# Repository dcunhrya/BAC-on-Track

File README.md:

# BAC-on-Track
Wearable Breathalyzer connected to an app to detect BAC levels for college students

This repo contains:
Circuit schematics from KiCAD,
PCB Layout from KiCAD,
OnShape CAD design

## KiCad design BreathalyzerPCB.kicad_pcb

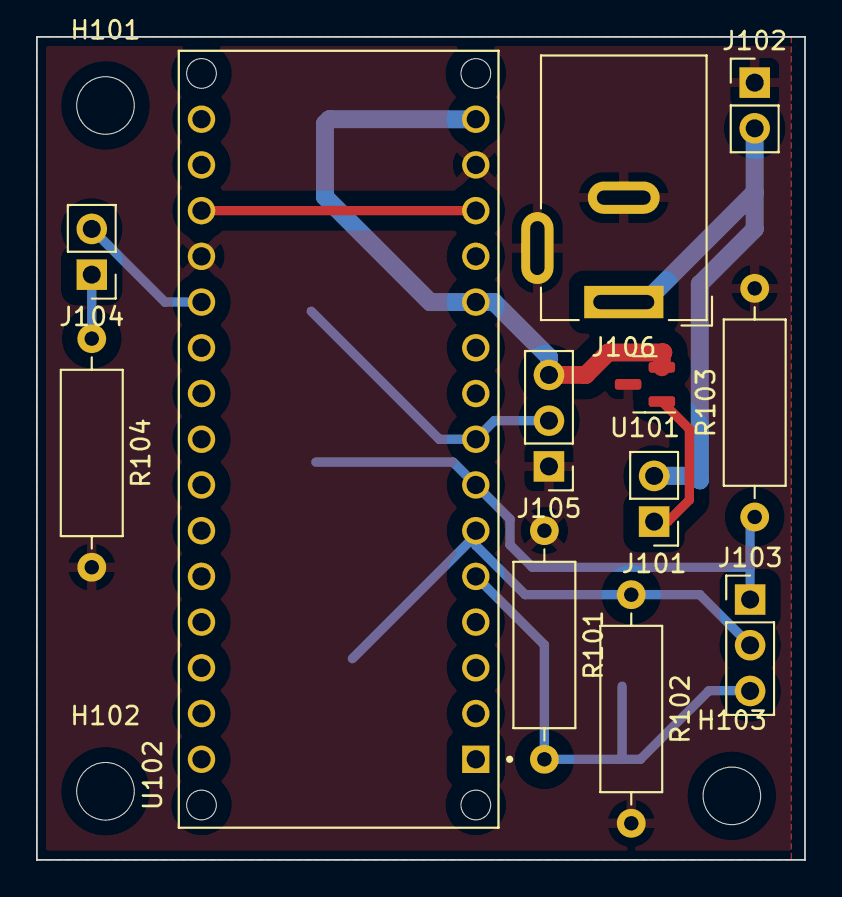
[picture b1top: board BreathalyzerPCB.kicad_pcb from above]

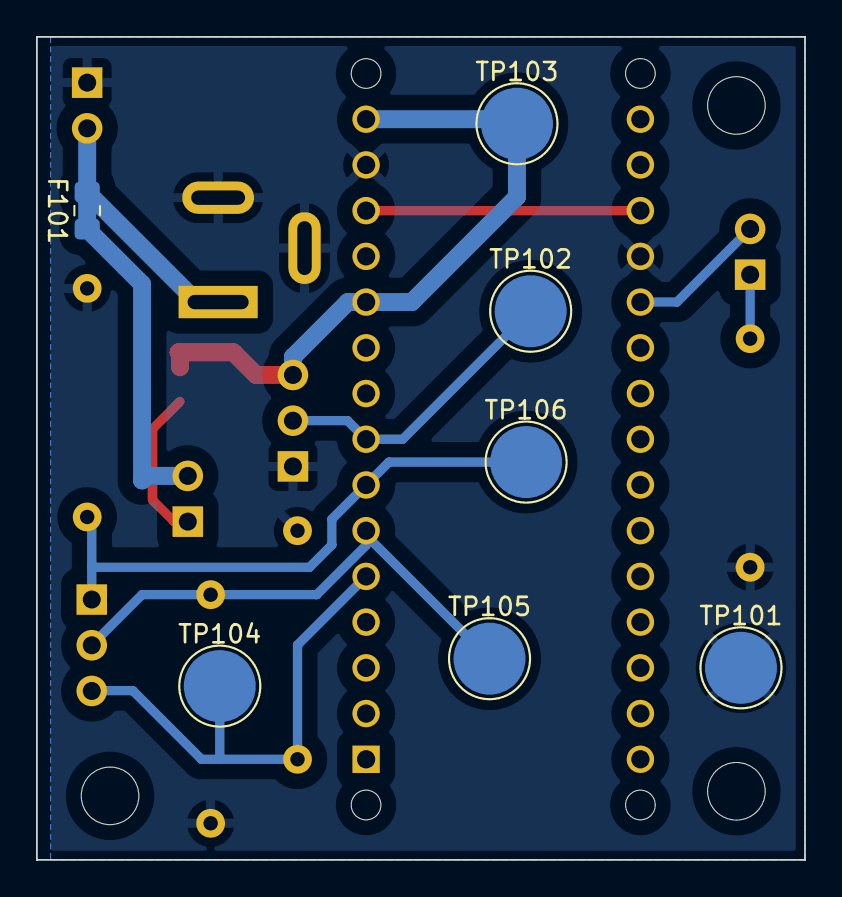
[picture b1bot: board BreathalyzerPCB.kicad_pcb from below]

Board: 2 copper layers, 42.7 x 45.7 mm, 22 parts (7 on the bottom side), 10 nets.

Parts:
F101: Fuse; Fuse_0805_2012Metric_Pad1.15x1.40mm_HandSolder
H101, H102, H103: MountingHole; MountingHole_3.2mm_M3
J101: Power Switch; PinHeader_1x02_P2.54mm_Vertical
J102: Battery; PinHeader_1x02_P2.54mm_Vertical
J103: RGBConn; PinHeader_1x03_P2.54mm_Vertical
J104: Read LED; PinHeader_1x02_P2.54mm_Vertical
J105: MQ3; PinHeader_1x03_P2.54mm_Vertical
J106: Barrel_Jack_Switch; BarrelJack_Wuerth_6941xx301002
R101, R102, R103, R104: 220; R_Axial_DIN0309_L9.0mm_D3.2mm_P12.70mm_Horizontal
TP101: GND; TestPoint_Pad_D4.0mm
TP102: AnalogMQ3; TestPoint_Pad_D4.0mm
TP103: VCC; TestPoint_Pad_D4.0mm
TP104: BattLED1Test; TestPoint_Pad_D4.0mm
TP105: BattLED2Test; TestPoint_Pad_D4.0mm
TP106: BattLED3Test; TestPoint_Pad_D4.0mm
U101: MAX6105; SOT-23
U102: ABX00030; MODULE_ABX00030

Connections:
+6V: F101.1, F101.2, J101.2, J102.2, J106.1
/BattLED1: J103.3, R101.2, TP104.1, U102.5 (A1)
/BattLED2: J103.2, R102.1, TP105.1, U102.6 (A2)
/BattLED3: J103.1, R103.1, TP106.1, U102.7 (A3)
/MQ3Analog: J105.2, TP102.1, U102.8 (A4/SDA)
/ReadLED: J104.2, U102.20 (D2)
/Switch: J101.1, U101.1 (IN)
GND: J102.1, J105.1, J106.2, J106.3, R101.1, R102.2, R103.2, R104.2, TP101.1, U101.3 (GND), U102.14 (GND), U102.19 (GND)
unnamed: J104.1, R104.1
VCC: J105.3, TP103.1, U101.2 (OUT), U102.11 (A7), U102.15 (VIN)

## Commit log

2023-02-28 v1.1
2023-03-05 v2.1.0
2023-03-05 v3.0.0
2023-03-06 v3.1.0
2023-03-10 v4.1.0
2023-03-26 v4.4.0
2023-07-26 remove zip
2023-07-26 removed zip
2023-07-26 restructure
